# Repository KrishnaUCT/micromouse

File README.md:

# Project Description

This project focuses on the power subsystem of a micro mouse.

# Requirements
This section was extracted from the project description.

- Operate up to 4 motors bidirectionally with the pins available to you (listed in the power pinout
table). You will need to control 2x brushed DC motors which could each draw 200mA at the
highest voltage of a 1S1P battery (the battery is further specified in the battery section).
The other 2x motors are for the auxiliary connection and need to operate 500mA each.
- Place an INA219 for monitoring the battery on the I2C Bus and configure it correctly with
respect to the hardware (cannot have BOTH A0 AND A1 on GND)
- Charge the battery from the 9V input pin (listed in the power pinout table).
- Have two charging modes for a higher and lower charging current for the battery (200mA, and
approximately 600mA ±100mA from the battery perspective.
- Integrate USB C and get 9V out of the USB Host
- Provide 2x External Load Switching at 1A each (High Side connected to your 5V)
- Provide a 3V3 5% accuracy (300mA max) and 5V Out 5% accuracy (1.5A max)
- Provide an ON/OFF switch. OFF state: battery draw <30uA. ON state: can provide your robot
peak current of 2A. The switch needs to shut down 5V and 3V3.

# Usage

To view the source KiCAD filese, clone the repository and open in KiCAD v9.

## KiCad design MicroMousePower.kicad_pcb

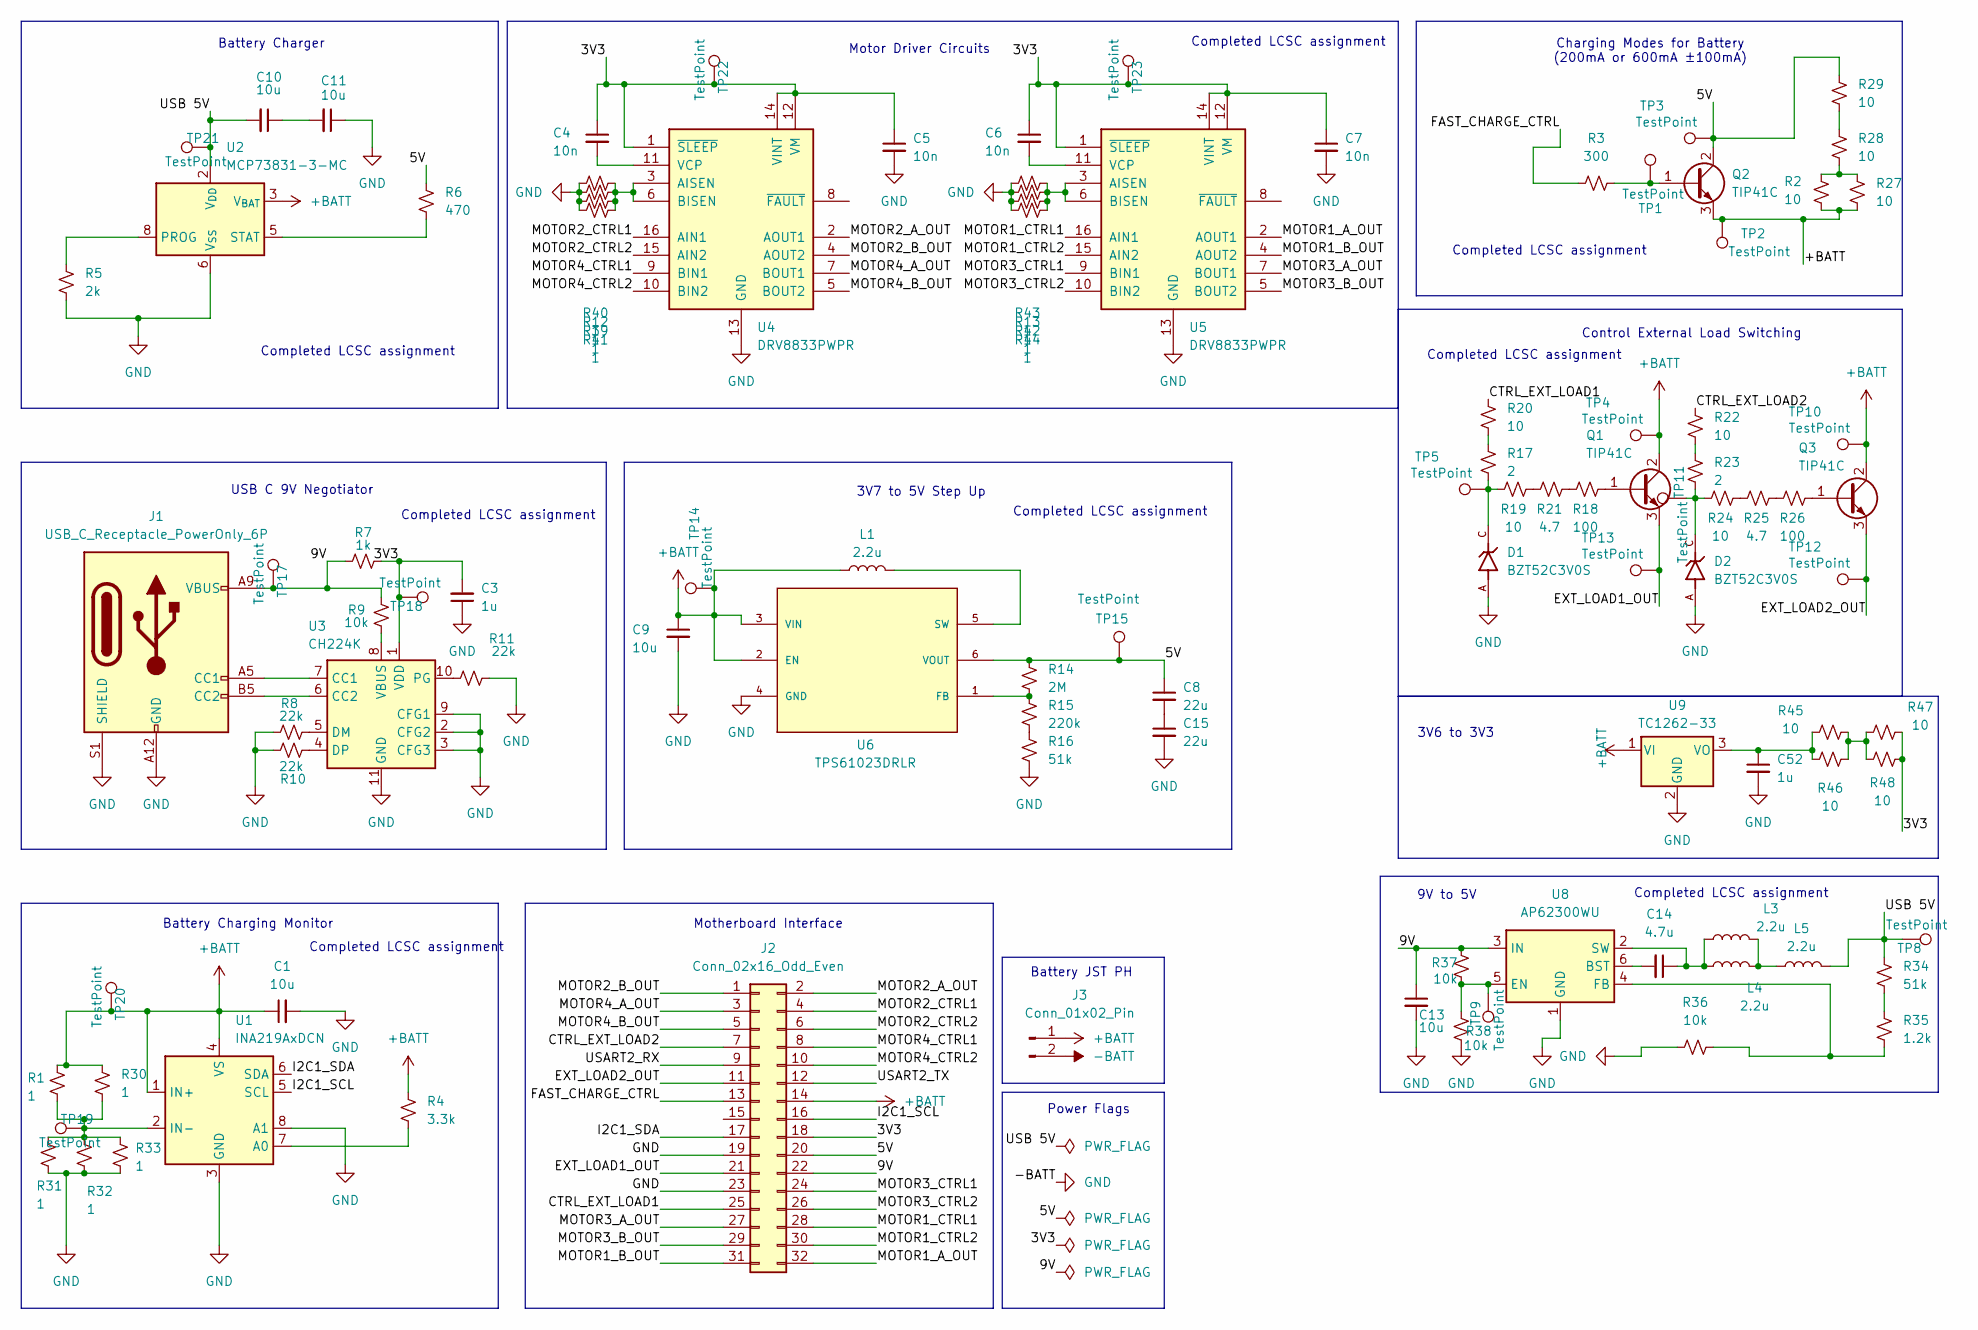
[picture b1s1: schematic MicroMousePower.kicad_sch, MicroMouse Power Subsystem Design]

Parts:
C1, C9, C10, C11, C13: 10u; C_0805_2012Metric; LCSC C15850
C3, C52: 1u; C_0402_1005Metric; LCSC C52923
C4, C5, C6, C7: 10n; C_0805_2012Metric; LCSC C15195
C8, C15: 22u; C_1206_3216Metric; LCSC C12891
C14: 4.7u; C_0402_1005Metric; LCSC C1569
D1, D2: BZT52C3V0S; D_SOD-323; PARTREV H2212; LCSC C19077436
J1: USB_C_Receptacle_PowerOnly_6P; USB_C_Receptacle_GCT_USB4125-xx-x_6P_TopMnt_Horizontal; LCSC C168701
J2: Conn_02x16_Odd_Even; PinHeader_2x16_P2.54mm_Vertical; LCSC C5307343
J3: Conn_01x02_Pin; JST_PH_B2B-PH-K_1x02_P2.00mm_Vertical; LCSC C131337
L1, L3, L4, L5: 2.2u; L_Cenker_CKCS4020; LCSC C135262
Q1, Q2, Q3: TIP41C; TO-220-3_Vertical; LCSC C92603
R1, R12, R13, R30, R31, R32, R33, R39, R40, R41, R42, R43, R44: 1; R_0603_1608Metric; LCSC C22936
R2, R27, R28, R29, R45, R46, R47, R48: 10; R_1206_3216Metric; LCSC C47019
R3: 300; R_1206_3216Metric; LCSC C17887
R4: 3.3k; R_0805_2012Metric; LCSC C26010
R5: 2k; R_0805_2012Metric; LCSC C17604
R6: 470; R_0805_2012Metric; LCSC C17710
R7: 1k; R_1206_3216Metric; LCSC C4410
R8, R10: 22k; R_0805_2012Metric; LCSC C17560
R9, R36, R37, R38: 10k; R_1206_3216Metric; LCSC C17902
R11: 22k; R_0805_2012Metric; LCSCf C17560
R14: 2M; R_0603_1608Metric; LCSC C22976
R15: 220k; R_0805_2012Metric; LCSC C17556
R16, R34: 51k; R_0805_2012Metric; LCSC C17737
R17, R23: 2; R_0201_0603Metric; LCSC C22977
R18, R26: 100; R_1206_3216Metric; LCSC C17901
R19, R20, R22, R24: 10; R_1206_3216Metric; LCSC C17903
R21: 4.7; R_0603_1608Metric; LCSC C23164
R25: 4.7; R_0603_1608Metric; LCSC C17903
R35: 1.2k; R_0805_2012Metric; LCSC C17379
TP1, TP2, TP3, TP4, TP5, TP8, TP9, TP10, TP11, TP12, TP13, TP14, TP15, TP17, TP18, TP19, TP20, TP21, TP22, TP23: TestPoint; TestPoint_Pad_D1.0mm
U1: INA219AxDCN; SOT-23-8; LCSC C87469
U2: MCP73831-3-MC; DFN-8-1EP_3x2mm_P0.5mm_EP1.7x1.4mm; LCSC C635038
U3: CH224K; SSOP-10-1EP_3.9x4.9mm_P1mm_EP2.1x3.3mm; LCSC C970725
U4, U5: DRV8833PWPR; TSSOP-16_4.4x5mm_P0.65mm; LCSC C50506
U6: TPS61023DRLR; SOT-563; MANUFACTURER_PART_NUMBER TPS61023DRLR; DigiKey_Part_Number 296-TPS61023DRLRTR-ND
U8: AP62300WU; TSOT-23-6; LCSC C1880390
U9: TC1262-33; SOT-223-3_TabPin2; LCSC C638655

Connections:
+BATT: C1.1, C9.1, J2.14, J3.1, L1.1, Q1.2 (C), Q2.3 (E), Q3.2 (C), R1.1, R2.2, R4.1, R27.2, R30.1, TP2.1, TP4.1, TP10.1, TP14.1, TP20.1, U1.1 (IN+), U1.4 (VS), U2.3 (V_{BAT}), U2.4 (V_{BAT}), U6.2 (EN), U6.3 (VIN), U9.1 (VI); also elsewhere on the board
-BATT: C1.2, C3.1, C5.2, C7.2, C9.2, C11.1, C13.2, C15.2, C52.2, D1.A, D2.A, J1.A12 (GND), J1.B12 (GND), J1.S1 (SHIELD), J2.19, J2.23, J3.2, R5.2, R8.1, R10.2, R11.2, R12.1, R13.1, R16.2, R31.2, R32.2, R33.2, R36.1, R38.1, R39.1, R40.1, R41.1, R42.1, R43.1, R44.1, U1.3 (GND), U1.8 (A1), U2.6 (V_{SS}), U3.2 (CFG2), U3.3 (CFG3), U3.9 (CFG1), U3.11 (GND), U4.13 (GND), U5.13 (GND), U6.4 (GND), U8.1 (GND), U9.2 (GND); also elsewhere on the board
/3V3: C3.2, C4.1, C5.1, C6.1, C7.1, J2.18, R7.2, R47.2, R48.2, TP18.1, TP22.1, TP23.1, U3.1 (VDD), U4.1 (~SLEEP), U4.12 (VM), U4.14 (VINT), U5.1 (~SLEEP), U5.12 (VM), U5.14 (VINT); also elsewhere on the board
/5V: C8.1, J2.20, Q2.2 (C), R6.1, R14.1, R29.1, TP3.1, TP15.1, U6.6 (VOUT)
/9V: C13.1, J1.A9 (VBUS), J1.B9 (VBUS), J2.22, R7.1, R9.1, R37.2, TP17.1, U8.3 (IN)
/CTRL_EXT_LOAD1: J2.25, R20.1
/CTRL_EXT_LOAD2: J2.7, R22.1
/EXT_LOAD1_OUT: J2.21, Q1.3 (E), TP13.1
/EXT_LOAD2_OUT: J2.11, Q3.3 (E), TP12.1
/FAST_CHARGE_CTRL: J2.13, R3.1
/I2C1_SCL: J2.16, U1.5 (SCL)
/I2C1_SDA: J2.17, U1.6 (SDA)
/MOTOR1_A_OUT: J2.32, U5.2 (AOUT1)
/MOTOR1_B_OUT: J2.31, U5.4 (AOUT2)
/MOTOR1_CTRL1: J2.28, U5.16 (AIN1)
/MOTOR1_CTRL2: J2.30, U5.15 (AIN2)
/MOTOR2_A_OUT: J2.2, U4.2 (AOUT1)
/MOTOR2_B_OUT: J2.1, U4.4 (AOUT2)
/MOTOR2_CTRL1: J2.4, U4.16 (AIN1)
/MOTOR2_CTRL2: J2.6, U4.15 (AIN2)
/MOTOR3_A_OUT: J2.27, U5.7 (BOUT1)
/MOTOR3_B_OUT: J2.29, U5.5 (BOUT2)
/MOTOR3_CTRL1: J2.24, U5.9 (BIN1)
/MOTOR3_CTRL2: J2.26, U5.10 (BIN2)
/MOTOR4_A_OUT: J2.3, U4.7 (BOUT1)
/MOTOR4_B_OUT: J2.5, U4.5 (BOUT2)
/MOTOR4_CTRL1: J2.8, U4.9 (BIN1)
/MOTOR4_CTRL2: J2.10, U4.10 (BIN2)
/USART2_RX: J2.9
/USART2_TX: J2.12
/USB 5V: C10.2, L5.2, R34.1, TP8.1, TP21.1, U2.1 (V_{DD}), U2.2 (V_{DD})
unnamed: C10.1, C11.2
unnamed: C8.2, C15.1
unnamed: D1.C, R17.2, R19.1, TP5.1
unnamed: D2.C, R23.2, R24.1, TP11.1
unnamed: J1.A5 (CC1), U3.7 (CC1)
unnamed: J1.B5 (CC2), U3.6 (CC2)
unnamed: L3.2, L4.2, L5.1
unnamed: Q1.1 (B), R18.2
unnamed: Q2.1 (B), R3.2, TP1.1
unnamed: Q3.1 (B), R26.2
unnamed: R2.1, R27.1, R28.2
unnamed: R15.2, R16.1
unnamed: R17.1, R20.2
unnamed: R18.1, R21.2
unnamed: R19.2, R21.1
unnamed: R22.2, R23.1
unnamed: R24.2, R25.1
unnamed: R25.2, R26.1
unnamed: R28.1, R29.2
unnamed: R34.2, R35.1
unnamed: R45.2, R46.2, R47.1, R48.1
unnamed: R4.2, U1.7 (A0)
unnamed: R1.2, R30.2, R31.1, R32.1, R33.1, TP19.1, U1.2 (IN-)
unnamed: R5.1, U2.8 (PROG)
unnamed: R6.2, U2.5 (STAT)
unnamed: R8.2, U3.5 (DM)
unnamed: R10.1, U3.4 (DP)
unnamed: R11.1, U3.10 (PG)
unnamed: R9.2, U3.8 (VBUS)
unnamed: R12.2, R39.2, R40.2, R41.2, U4.3 (AISEN), U4.6 (BISEN)
unnamed: C4.2, U4.11 (VCP)
unnamed: R13.2, R42.2, R43.2, R44.2, U5.3 (AISEN), U5.6 (BISEN)
unnamed: C6.2, U5.11 (VCP)
unnamed: R14.2, R15.1, U6.1 (FB)
unnamed: L1.2, U6.5 (SW)
unnamed: C14.2, U8.6 (BST)
unnamed: R37.1, R38.2, TP9.1, U8.5 (EN)
unnamed: R35.2, R36.2, U8.4 (FB)
unnamed: C14.1, L3.1, L4.1, U8.2 (SW)
unnamed: C52.1, R45.1, R46.1, U9.3 (VO)

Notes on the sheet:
Battery Charging Monitor
Completed LCSC assignment
Power Flags
Motor Driver Circuits
3V6 to 3V3
Charging Modes for Battery (200mA or 600mA ±100mA)
Battery JST PH
USB C 9V Negotiator
9V to 5V
3V7 to 5V Step Up
Motherboard Interface
Battery Charger
Control External Load Switching

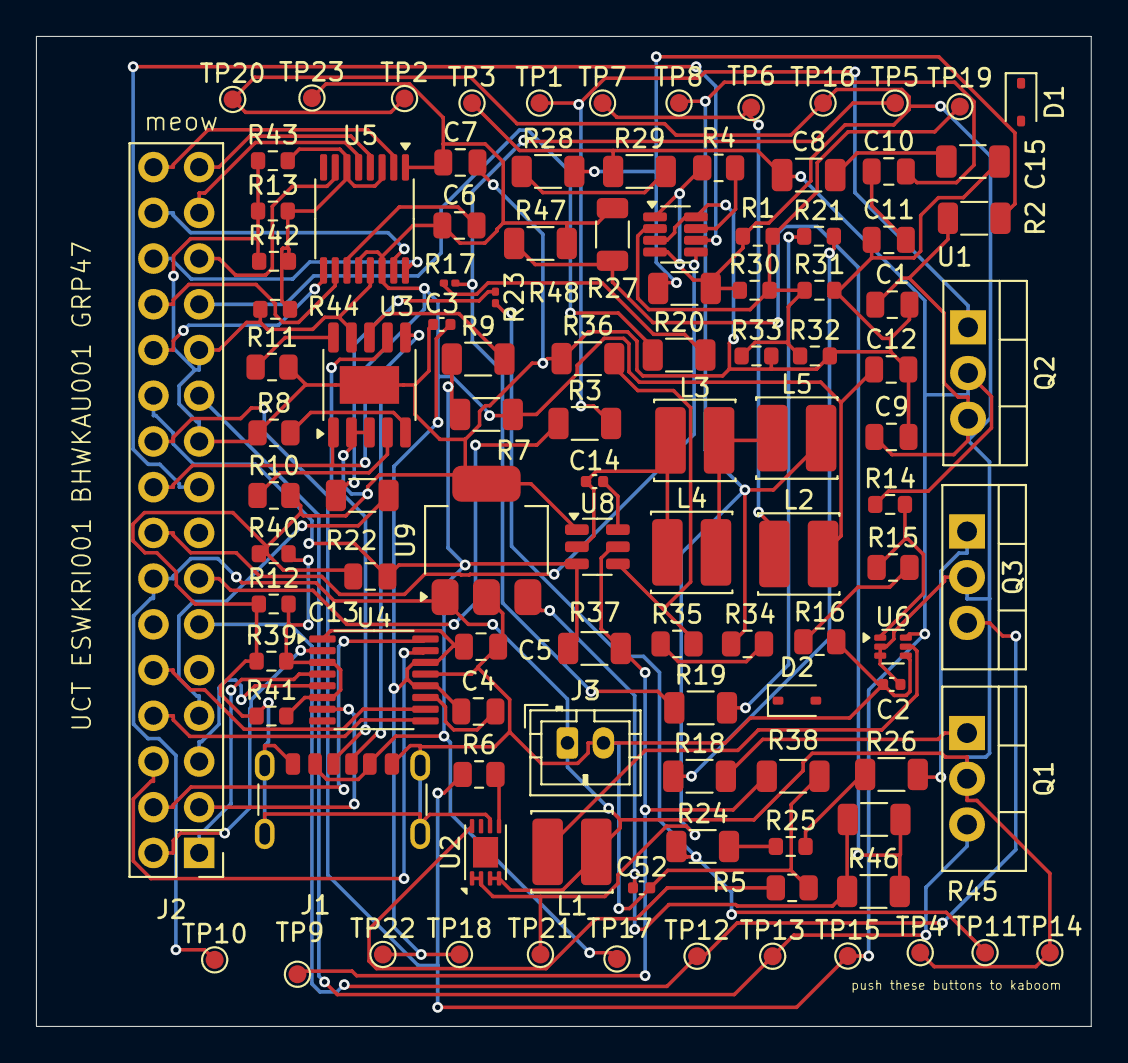
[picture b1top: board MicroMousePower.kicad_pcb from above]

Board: 2 copper layers, 58.6 x 55.0 mm, 108 parts (0 on the bottom side), 70 nets.

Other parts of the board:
C2: 4.7u; C_0402_1005Metric
C12: 10u; C_0805_2012Metric
L2: 2.2u; L_Cenker_CKCS4020
TP6, TP7, TP16: TestPoint; TestPoint_Pad_D1.0mm

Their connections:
+BATT: C2.2, TP16.1; also elsewhere on the board
-BATT: C2.1, C12.2; also elsewhere on the board
/3V3: C12.1, L2.2; also elsewhere on the board
unnamed: L2.1, TP6.1, TP7.1

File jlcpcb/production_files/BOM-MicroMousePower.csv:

Comment,Designator,Footprint,LCSC,Quantity
22u,"C15,C8",C_1206_3216Metric,C12891,2
2.2u,"L1,L2,L3,L4,L5",L_Cenker_CKCS4020,C135262,5
10n,"C4,C5,C6,C7",C_0805_2012Metric,C15195,4
4.7u,"C14,C2",C_0402_1005Metric,C1569,2
10u,"C1,C10,C11,C13,C9",C_0805_2012Metric,C15850,5
10u,C12,C_0805_2012Metric,C1634,1
USB_C_Receptacle_PowerOnly_6P,J1,USB_C_Receptacle_GCT_USB4125-xx-x_6P_TopMnt_Horizontal,C168701,1
1.2k,R35,R_0805_2012Metric,C17379,1
220k,R15,R_0805_2012Metric,C17556,1
22k,"R10,R11,R8",R_0805_2012Metric,C17560,3
2k,R5,R_0805_2012Metric,C17604,1
470,R6,R_0805_2012Metric,C17710,1
51k,"R16,R34",R_0805_2012Metric,C17737,2
300,R3,R_1206_3216Metric,C17887,1
100,"R18,R26",R_1206_3216Metric,C17901,2
10k,"R36,R37,R38,R9",R_1206_3216Metric,C17902,4
10,"R19,R20,R22,R24,R25",R_1206_3216Metric,C17903,5
AP62300WU,U8,TSOT-23-6,C1880390,1
BZT52C3V0S,"D1,D2",D_SOD-323,C19077436,2
1,"R1,R12,R13,R30,R31,R32,R33,R39,R40,R41,R42,R43,R44",R_0603_1608Metric,C22936,13
2M,R14,R_0603_1608Metric,C22976,1
2,"R17,R23",R_0201_0603Metric,C22977,2
4.7,R21,R_0603_1608Metric,C23164,1
3.3k,R4,R_0805_2012Metric,C26010,1
1k,R7,R_1206_3216Metric,C4410,1
10,"R2,R27,R28,R29,R45,R46,R47,R48",R_1206_3216Metric,C47019,8
DRV8833PWPR,"U4,U5",TSSOP-16_4.4x5mm_P0.65mm,C50506,2
1u,"C3,C52",C_0402_1005Metric,C52923,2
MCP73831-3-MC,U2,DFN-8-1EP_3x2mm_P0.5mm_EP1.7x1.4mm,C635038,1
TC1262-33,U9,SOT-223-3_TabPin2,C638655,1
INA219AxDCN,U1,SOT-23-8,C87469,1
TPS61023DRLR,U6,SOT-563,C919459,1
TIP41C,"Q1,Q2,Q3",TO-220-3_Vertical,C92603,3
CH224K,U3,SSOP-10-1EP_3.9x4.9mm_P1mm_EP2.1x3.3mm,C970725,1

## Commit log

2025-03-22 init: empty project
2025-03-22 meow meow meow
    pss pss
2025-03-22 woof woof woof
2025-03-22 r with comment
2025-03-22 (text "higher and lower charging current for the battery (200mA or 600mA ±100mA)"
    not sure about how its gonna be connected later,just uploaded schematic
2025-03-24 removed test files
2025-03-24 completed INA219 integration
2025-03-24 added battery charging circuit
2025-03-24 checking if it works
2025-03-25 TP+ TIP 31C
2025-03-25 lines only
2025-03-26 MEOW?
2025-03-27 organized circuit sections, added schematic metadata
2025-03-27 integrated USB C 9V negotiator
2025-03-27 defined motherboard interface and added motor driver IC
2025-03-27 connected motor driver circuit
2025-03-27 power flag defintions for ERC
2025-03-27 template for step down IC
2025-03-27 added 3V6 to 3V3 step down
2025-03-27 added current sources
2025-03-28 added LCSC values to all components
2025-03-28 completed schematic with LCSC codes
2025-03-28 fixed ERC errors
2025-03-28 fixed more ERC errors
2025-03-28 Test points
    test points
2025-03-28 meow idk?
    pss pss
2025-03-28 added testpoints
2025-03-28 fixed misc oversights and assigned footprints
2025-03-28 added missing LCSC codes
2025-03-28 fixed yet another mislabeled LCSC code
2025-03-28 tried my best lol
    dont forget on WA
2025-03-28 try 2
    try ?
2025-03-28 updated pinheader footprint
2025-03-28 rearranged pcb layout
2025-03-28 added routing
2025-03-28 moved tips
2025-03-28 added final routing
2025-03-28 rotated for bending
2025-03-28 added final final routing
2025-03-28 moved resistors to overcome disconnect
2025-03-28 exported fv4
2025-03-28 routed fv4
2025-03-28 fixed another disconnect
2025-03-28 completed final routing and generated JLCPCB production files
2025-03-28 updated schematic due to ordering error
2025-03-28 the pain never ends
2025-03-28 there is light at the end
2025-03-29 final submission
2025-03-29 deleted routing iterations
2025-04-23 cleaned up schematic
2025-05-16 added comments

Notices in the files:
parts and their libraries:
COPYRIGHT: Copyright (C) 2022 Ultra Librarian. All rights reserved.
